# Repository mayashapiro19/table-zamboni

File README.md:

# Table Zamboni

## Hardware Block Diagram
The image below shows a high-level block diagram of the hardware architecture.<br>

### Main PCB
The main PCB uses an ESP32-S3-WROOM-1-N8 module and includes power management circuitry, a USB to UART converter, motor driver, and an inertial measurement unit.

### Time-of-Flight Breakout Board

### Peripherals Breakout Board
The peripherals breakout board includes a push button and a WS2812B LED. The LED will be used at specific points to communicate things to the user. Because it will only be used for short periods of time, to save power, a load switch is used. The block diagram below illustrates the hardware architecture of the peripherals breakout board.<br>

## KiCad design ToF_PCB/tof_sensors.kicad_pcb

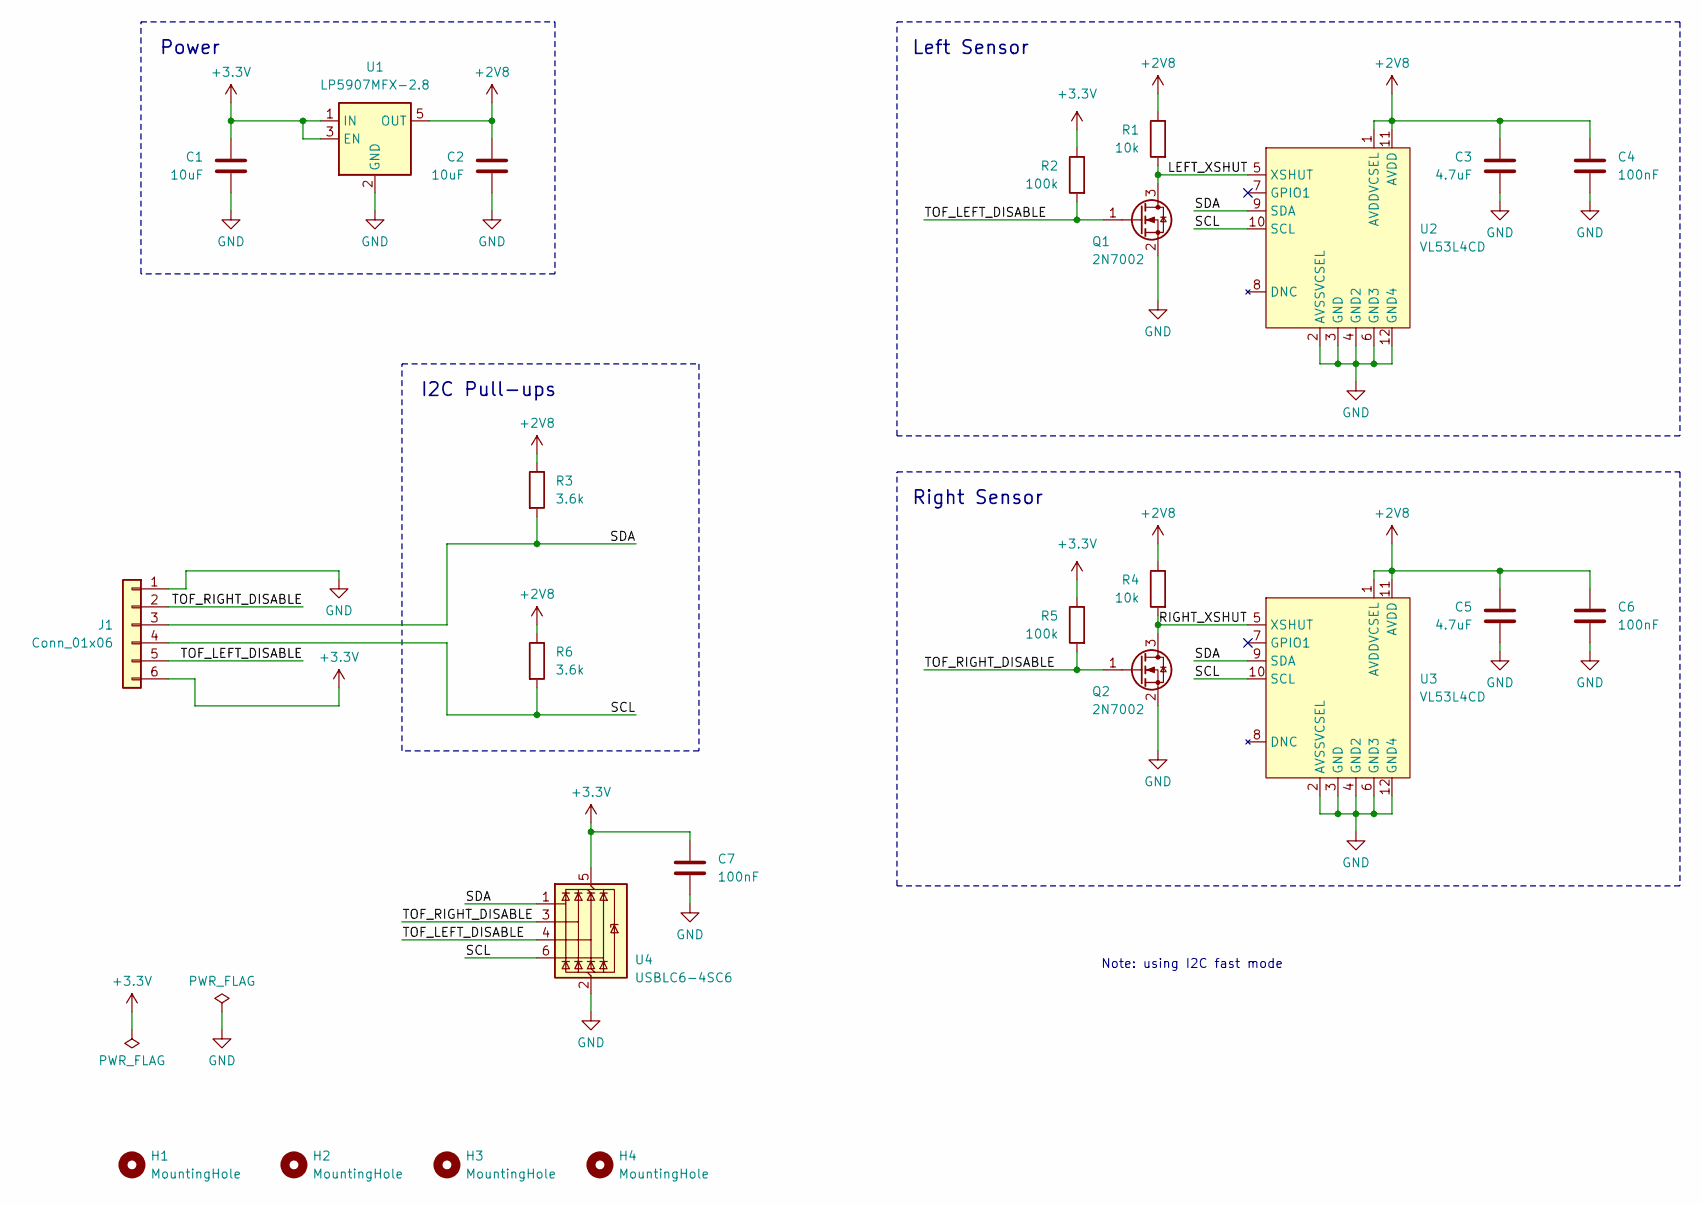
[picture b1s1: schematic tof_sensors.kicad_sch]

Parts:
C1: 10uF; C_0504_1310Metric
C2: 10uF; C_0805_2012Metric_Pad1.18x1.45mm_HandSolder
C3, C5: 4.7uF; C_0805_2012Metric_Pad1.18x1.45mm_HandSolder
C4, C6: 100nF; C_0805_2012Metric_Pad1.18x1.45mm_HandSolder
C7: 100nF; C_0201_0603Metric
H1, H2, H3, H4: MountingHole; MountingHole_2.5mm
J1: Conn_01x06; JST_SH_BM06B-SRSS-TB_1x06-1MP_P1.00mm_Vertical
Q1, Q2: 2N7002; SOT-23
R1, R4: 10k; R_0805_2012Metric_Pad1.20x1.40mm_HandSolder
R2, R5: 100k; R_0805_2012Metric_Pad1.20x1.40mm_HandSolder
R3, R6: 3.6k; R_0805_2012Metric_Pad1.20x1.40mm_HandSolder
U1: LP5907MFX-2.8; SOT-23-5
U2, U3: VL53L4CD
U4: USBLC6-4SC6; SOT-23-6

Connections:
+2V8: C2.1, C3.1, C4.1, C5.1, C6.1, R1.1, R3.1, R4.1, R6.1, U1.5 (OUT), U2.1 (AVDDVCSEL), U2.11 (AVDD), U3.1 (AVDDVCSEL), U3.11 (AVDD)
+3.3V: C1.1, C7.1, J1.6, R2.1, R5.1, U1.1 (IN), U1.3 (EN), U4.5 (VBUS)
/LEFT_XSHUT: Q1.3 (D), R1.2, U2.5 (XSHUT)
/RIGHT_XSHUT: Q2.3 (D), R4.2, U3.5 (XSHUT)
/SCL: J1.4, R6.2, U2.10 (SCL), U3.10 (SCL), U4.6 (I/O4)
/SDA: J1.3, R3.2, U2.9 (SDA), U3.9 (SDA), U4.1 (I/O1)
/TOF_LEFT_DISABLE: J1.5, Q1.1 (G), R2.2, U4.4 (I/O3)
/TOF_RIGHT_DISABLE: J1.2, Q2.1 (G), R5.2, U4.3 (I/O2)
GND: C1.2, C2.2, C3.2, C4.2, C5.2, C6.2, C7.2, J1.1, Q1.2 (S), Q2.2 (S), U1.2 (GND), U2.2 (AVSSVCSEL), U2.3 (GND), U2.4 (GND2), U2.6 (GND3), U2.12 (GND4), U3.2 (AVSSVCSEL), U3.3 (GND), U3.4 (GND2), U3.6 (GND3), U3.12 (GND4), U4.2 (GND)

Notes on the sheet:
Left Sensor
Power
I2C Pull-ups
Right Sensor
Note: using I2C fast mode

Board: 4 copper layers, 24 parts (2 on the bottom side), 9 nets, no tracks yet.

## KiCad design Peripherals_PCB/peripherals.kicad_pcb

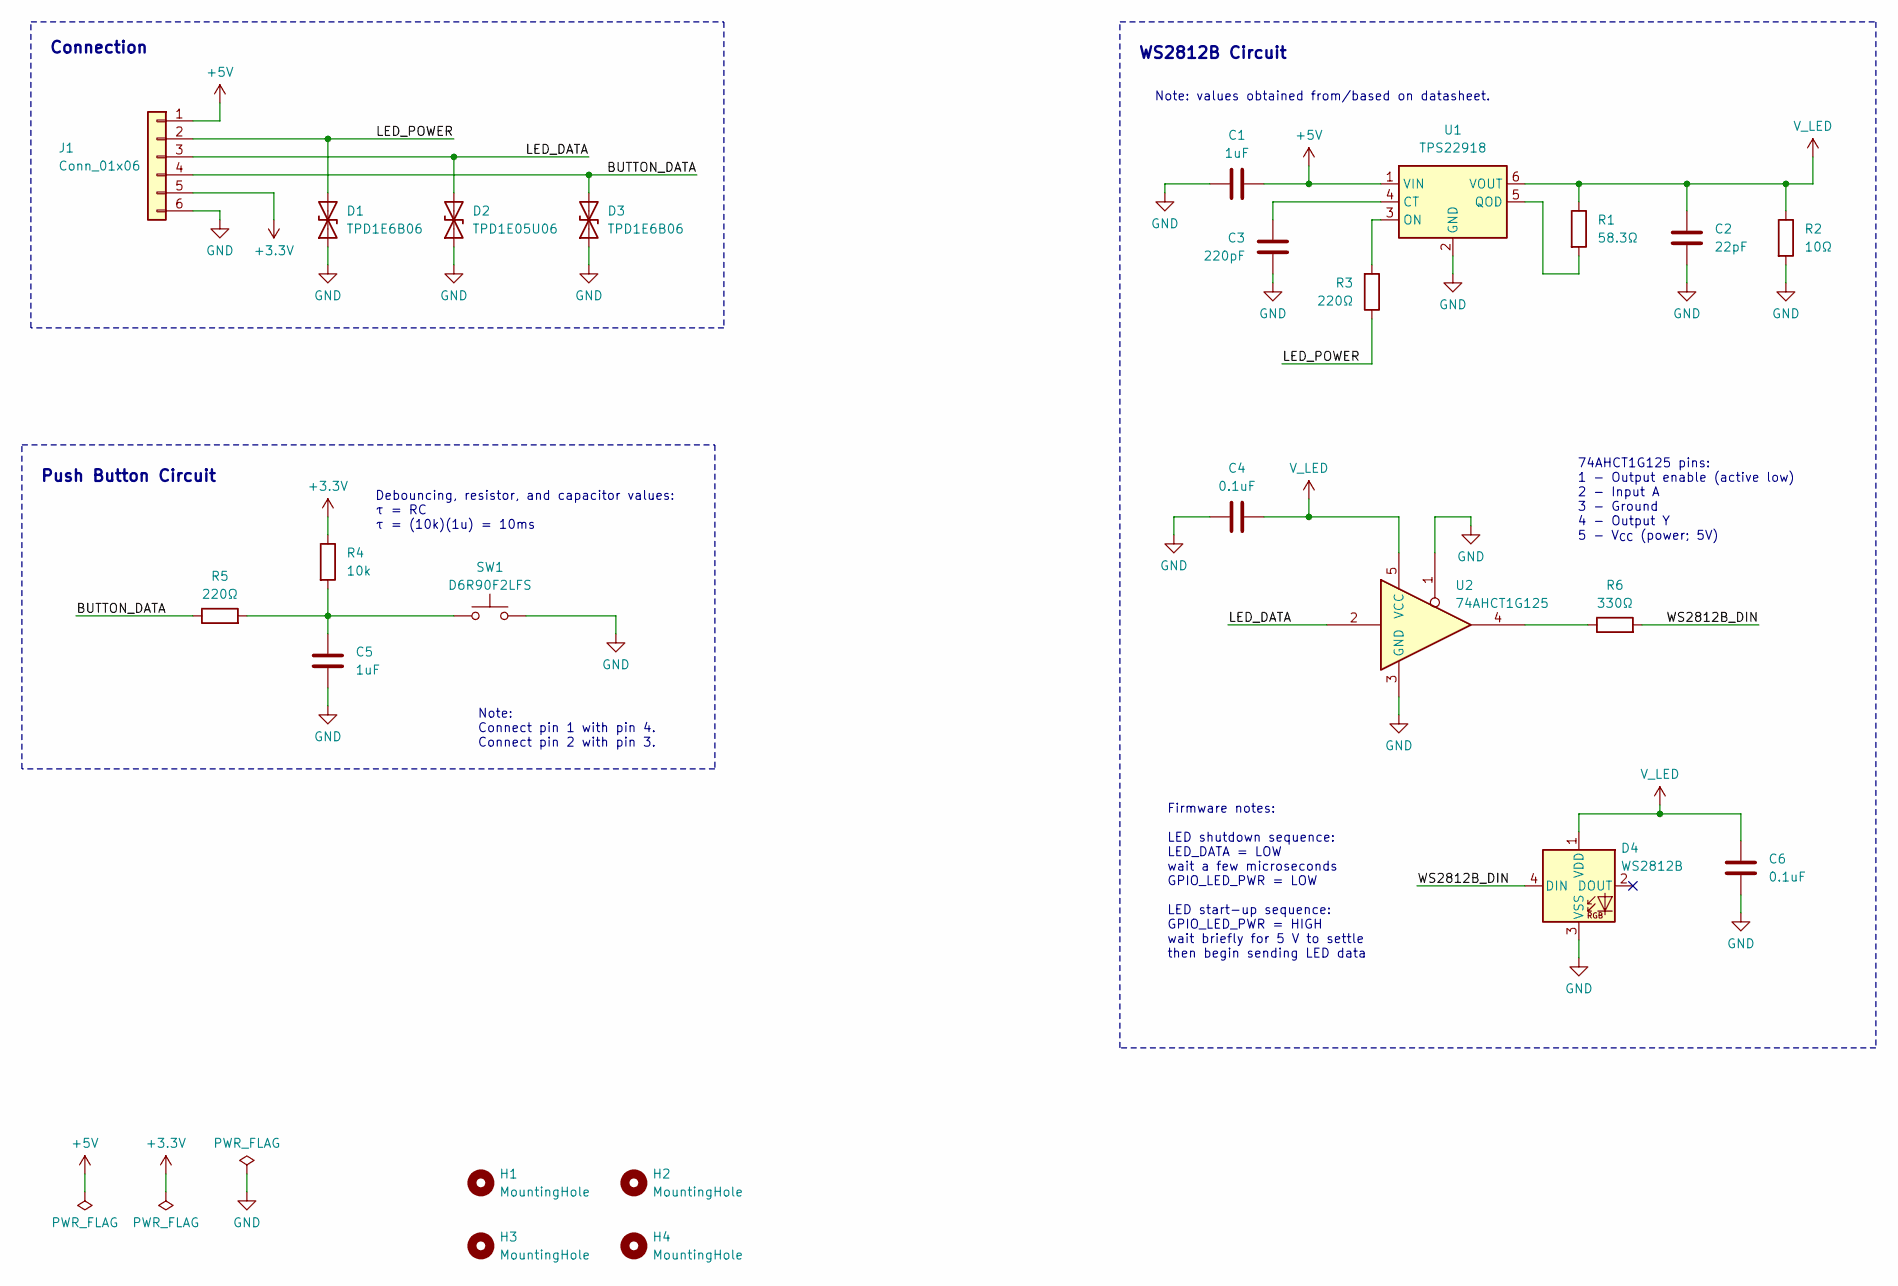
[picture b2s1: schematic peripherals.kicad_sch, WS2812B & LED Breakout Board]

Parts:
C1, C5: 1uF; C_0805_2012Metric_Pad1.18x1.45mm_HandSolder
C2: 22pF; C_0805_2012Metric_Pad1.18x1.45mm_HandSolder
C3: 220pF; C_0805_2012Metric_Pad1.18x1.45mm_HandSolder
C4, C6: 0.1uF; C_0805_2012Metric_Pad1.18x1.45mm_HandSolder
D1, D3: TPD1E6B06; TPD1E6B06_footprint
D2: TPD1E05U06
D4: WS2812B; COM-16347_SPK-M
H1, H2, H3, H4: MountingHole; MountingHole_3mm
J1: Conn_01x06; JST_SH_BM06B-SRSS-TB_1x06-1MP_P1.00mm_Vertical
R1: 58.3Ω; R_0805_2012Metric_Pad1.20x1.40mm_HandSolder
R2: 10Ω; R_0805_2012Metric_Pad1.20x1.40mm_HandSolder
R3, R5: 220Ω; R_0805_2012Metric_Pad1.20x1.40mm_HandSolder
R4: 10k; R_0805_2012Metric_Pad1.20x1.40mm_HandSolder
R6: 330Ω; R_0805_2012Metric_Pad1.20x1.40mm_HandSolder
SW1: D6R90F2LFS; D6R90_CNK
U1: TPS22918; DBV6_TEX-M
U2: 74AHCT1G125; DBV5-M

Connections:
+3.3V: J1.5, R4.1
+5V: C1.1, J1.1, U1.1 (VIN)
/BUTTON_DATA: D3.2 (A2), J1.4, R5.1
/LED_DATA: D2.2 (A2), J1.3, U2.2
/LED_POWER: D1.2 (A2), J1.2, R3.1
/WS2812B_DIN: D4.4 (DIN), R6.2
GND: C1.2, C2.1, C3.1, C4.1, C5.2, C6.2, D1.1 (A1), D2.1 (A1), D3.1 (A1), D4.3 (VSS), J1.6, R2.2, SW1.2, U1.2 (GND), U2.1, U2.3 (GND)
unnamed: C5.1, R4.2, R5.2, SW1.1
unnamed: R6.1, U2.4
unnamed: C3.2, U1.4 (CT)
unnamed: R3.2, U1.3 (ON)
unnamed: R1.2, U1.5 (QOD)
V_LED: C2.2, C4.2, C6.1, D4.1 (VDD), R1.1, R2.1, U1.6 (VOUT), U2.5 (VCC)

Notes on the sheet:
Note: Connect pin 1 with pin 4. Connect pin 2 with pin 3.
Debouncing, resistor, and capacitor values: τ = RC τ = (10k)(1u) = 10ms
WS2812B Circuit
Firmware notes: LED shutdown sequence: LED_DATA = LOW wait a few microseconds GPIO_LED_PWR = LOW LED start-up sequence: GPIO_LED_PWR = HIGH wait briefly for 5 V to settle then begin sending LED data
Push Button Circuit
Connection
74AHCT1G125 pins: 1 - Output enable (active low) 2 - Input A 3 - Ground 4 - Output Y 5 - V_{CC} (power; 5V)
Note: values obtained from/based on datasheet.

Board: 4 copper layers, 24 parts (2 on the bottom side), 13 nets, no tracks yet.
